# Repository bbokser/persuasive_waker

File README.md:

# persuasive_waker

Persuasive Waker is an open source hardware alarm clock that can't be snoozed or turned off. The alarm is deactivated via a remote key fob, which should be placed as far from the user's bed as possible. E.g. in the bathroom.

The KiCad design files are located in the [`hw`](hw) folder.

The STEP assembly is located [here](hw/step/).

If you just want STLs for printing, they're [here](hw/stl).

## BoM
| Item          | QTY| Source |
| --------------| ---|--|
| Case          | 1  | 3D Print |
| Screen Holder | 1  | 3D Print |
| Spacer        | 2  | 3D Print |
| M2.5x0.45-12-SHCS-SS304 | 4  | |
| M2.5x0.45-6-SHCS-SS304 | 4  | |
| M2.5x0.45-4-FHS-SS304 | 2 | |
| PRESSNUT-M2.5x0.45-SS304 | 2 | [Mouser](https://mou.sr/3FToM2v)|
| Battery Holder | 1 | [Mouser](https://mou.sr/4lddciV) |
| THRIN-M2.5X0.45-HS-PL-4L3.5D-BR | 8 | [Amazon](https://www.amazon.com/dp/B0DGPL6RWT)|
| E-Paper Display | 1 | [AliExpress](https://www.aliexpress.us/item/2251832627460771.html)|
| Key Fob | 1 | [AliExpress](https://www.aliexpress.us/item/2251832657961546.html) |
| Alarm PCB | 1 | Custom PCBA Order |
| Front Plate | 1 | Custom PCB Order  |
| Rear Plate | 1 | Custom PCB Order  |

## Mechanical Build
1. Print the case, screen holder, and two spacers.
2. Install the heat-set inserts in the case (x8).
3. Insert the PCB from the front.
4. Plug the E-paper display into the FPC connector.
5. Put the screen holder and spacers into position and then fold the display down onto it. Make sure the display is properly nestled in.
6. Holding the display down, put the front cover on.
7. Screw the front cover on with the M2.5x12 screws.
8. Using an arbor press, press the press-fit nuts into the rear cover.
9. Screw the battery holder onto the rear cover using the flat head screws and loctite. Insert AA batteries.
10. Plug the battery holder into the power connector on the back of the PCB.
11. Screw the rear cover on using the M2.5x6 screws.

## Firmware Setup
1. Install CircuitPython on your Pico by following [this](https://learn.adafruit.com/getting-started-with-raspberry-pi-pico-circuitpython/circuitpython) guide.
The last version tested with this device is [9.2.6.](https://adafruit-circuit-python.s3.amazonaws.com/bin/raspberry_pi_pico/en_US/adafruit-circuitpython-raspberry_pi_pico-en_US-9.2.6.uf2)

2. Install [circup](https://learn.adafruit.com/keep-your-circuitpython-libraries-on-devices-up-to-date-with-circup/prepare) on your computer.

3. Run the following commands to install all necessary libraries.

    ```
    circup bundle-add adafruit/circuitpython-fonts
    circup install adafruit_sht4x adafruit_ssd1680 adafruit_display_text adafruit_ds3231 adafruit_datetime adafruit_display_shapes font_ostrich_sans_black_24 font_ostrich_sans_black_60
    ```
4. Delete `code.py` from the Pico's storage.

5. Clone this repo onto your computer and copy+paste everything in the `src` folder to the Pico's storage.

6. The alarm clock should be functioning now.

## User Manual
See [here](user_manual.md).

### Upgrading from v3.0 to v3.1
1. Replace the old `src` files with the new ones on the `v3.1` branch.
2. Install [circup](https://learn.adafruit.com/keep-your-circuitpython-libraries-on-devices-up-to-date-with-circup/prepare) and run the following.
    ```
    circup bundle-add adafruit/circuitpython-fonts
    circup uninstall font_ostrich_sans_black_30 font_ostrich_sans_black_72
    circup install font_ostrich_sans_black_24 font_ostrich_sans_black_60
    circup update
    ```
    
    Alternatively, you can download the [requirements.txt](requirements.txt) and run the following:
    
    ```
    circup install -r /path/to/requirements.txt
    ```

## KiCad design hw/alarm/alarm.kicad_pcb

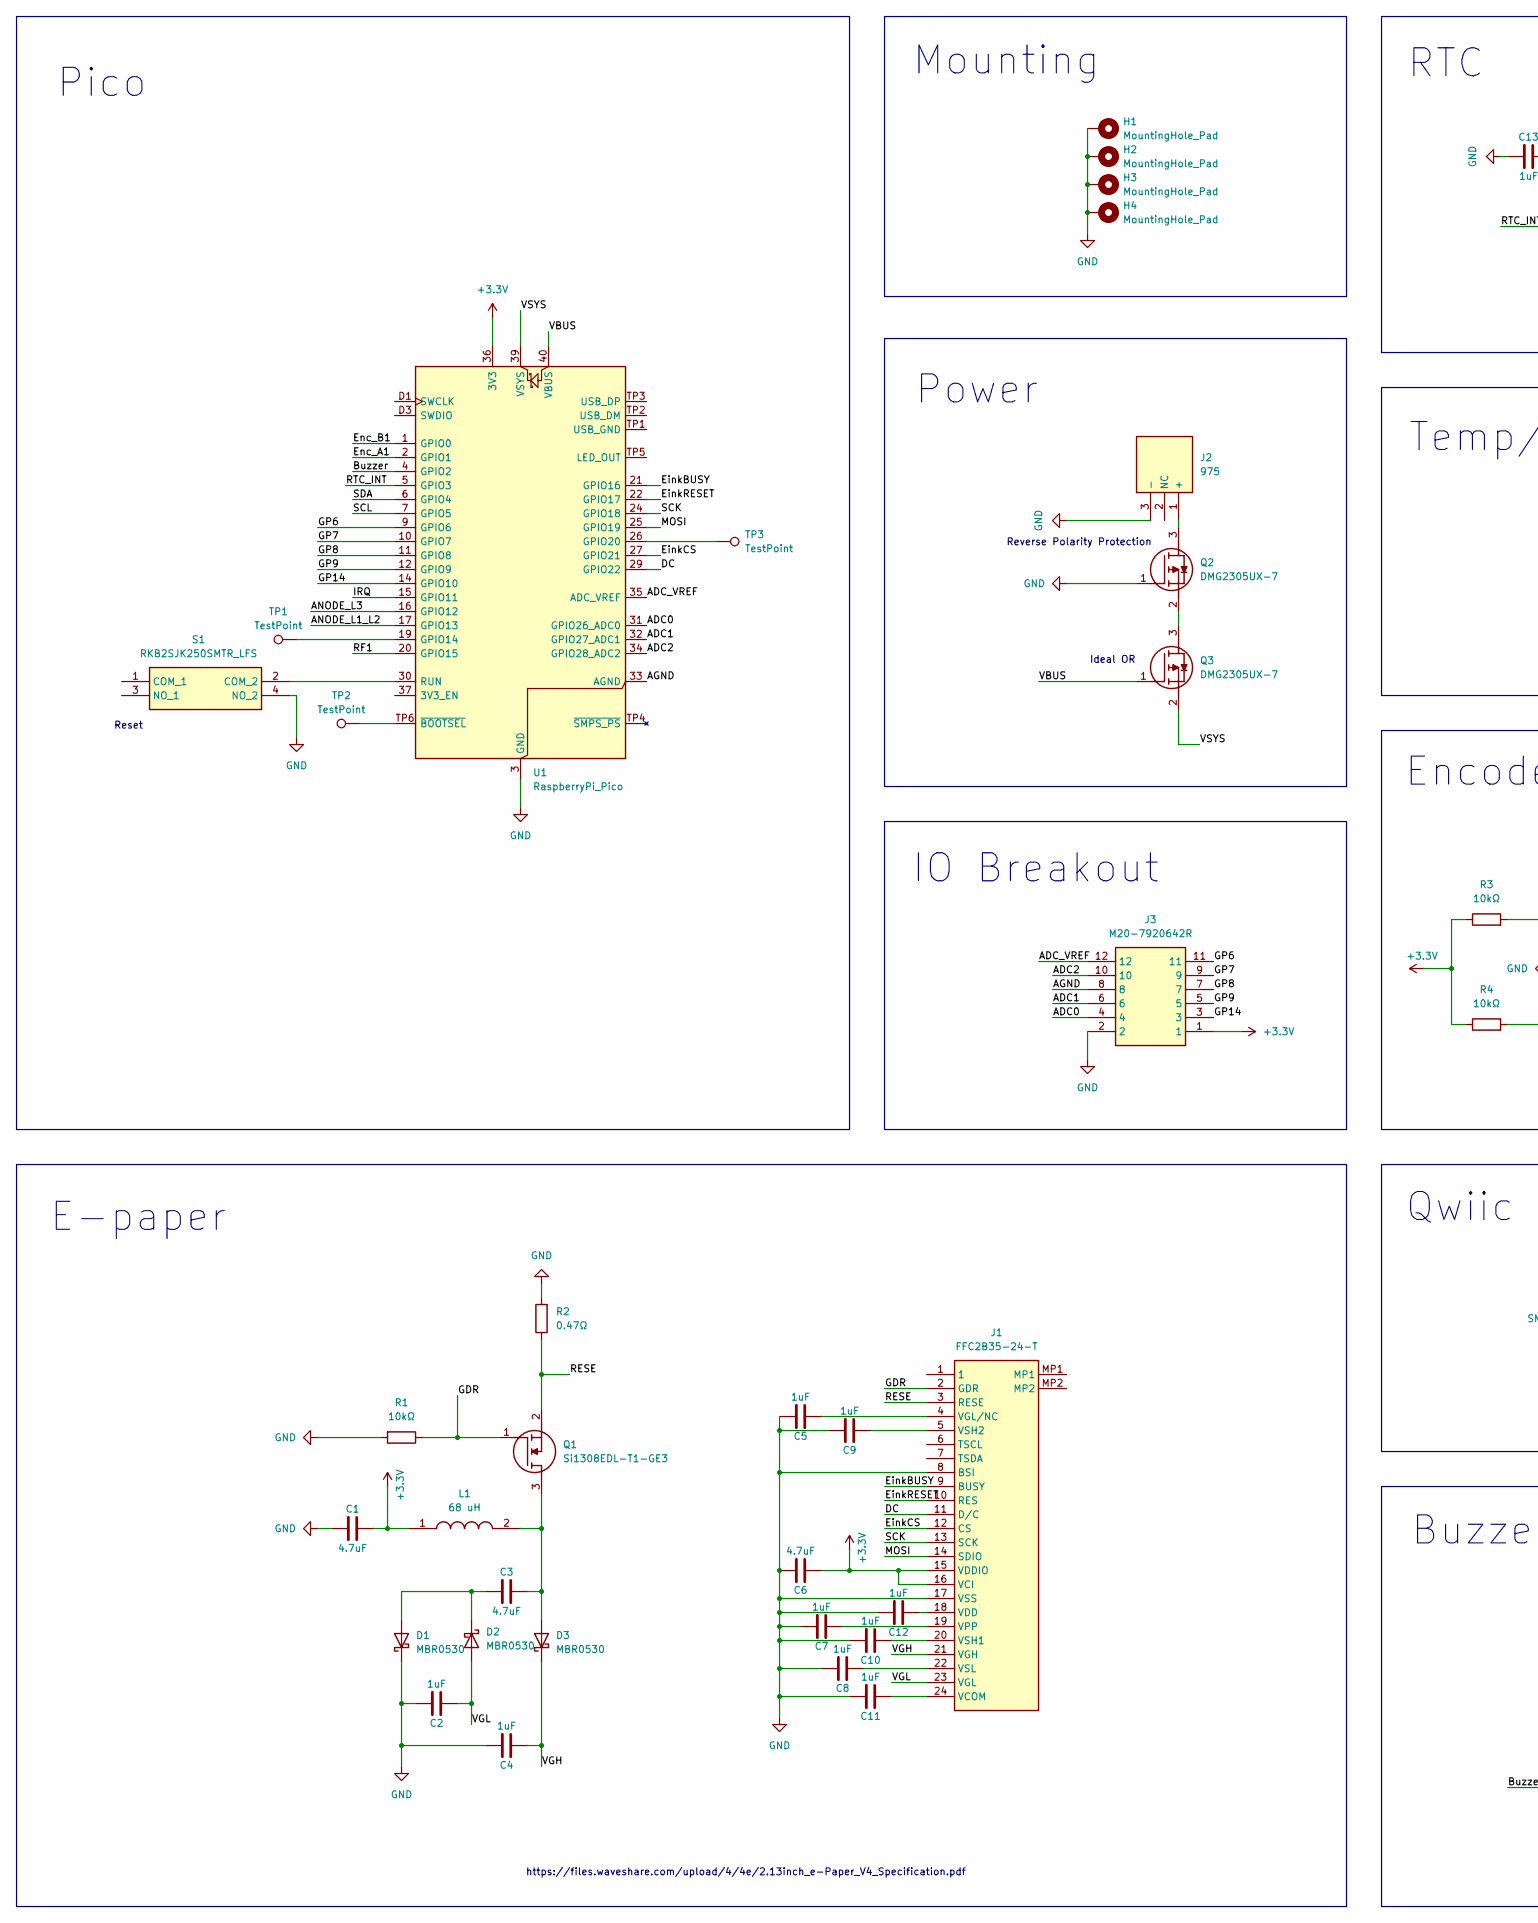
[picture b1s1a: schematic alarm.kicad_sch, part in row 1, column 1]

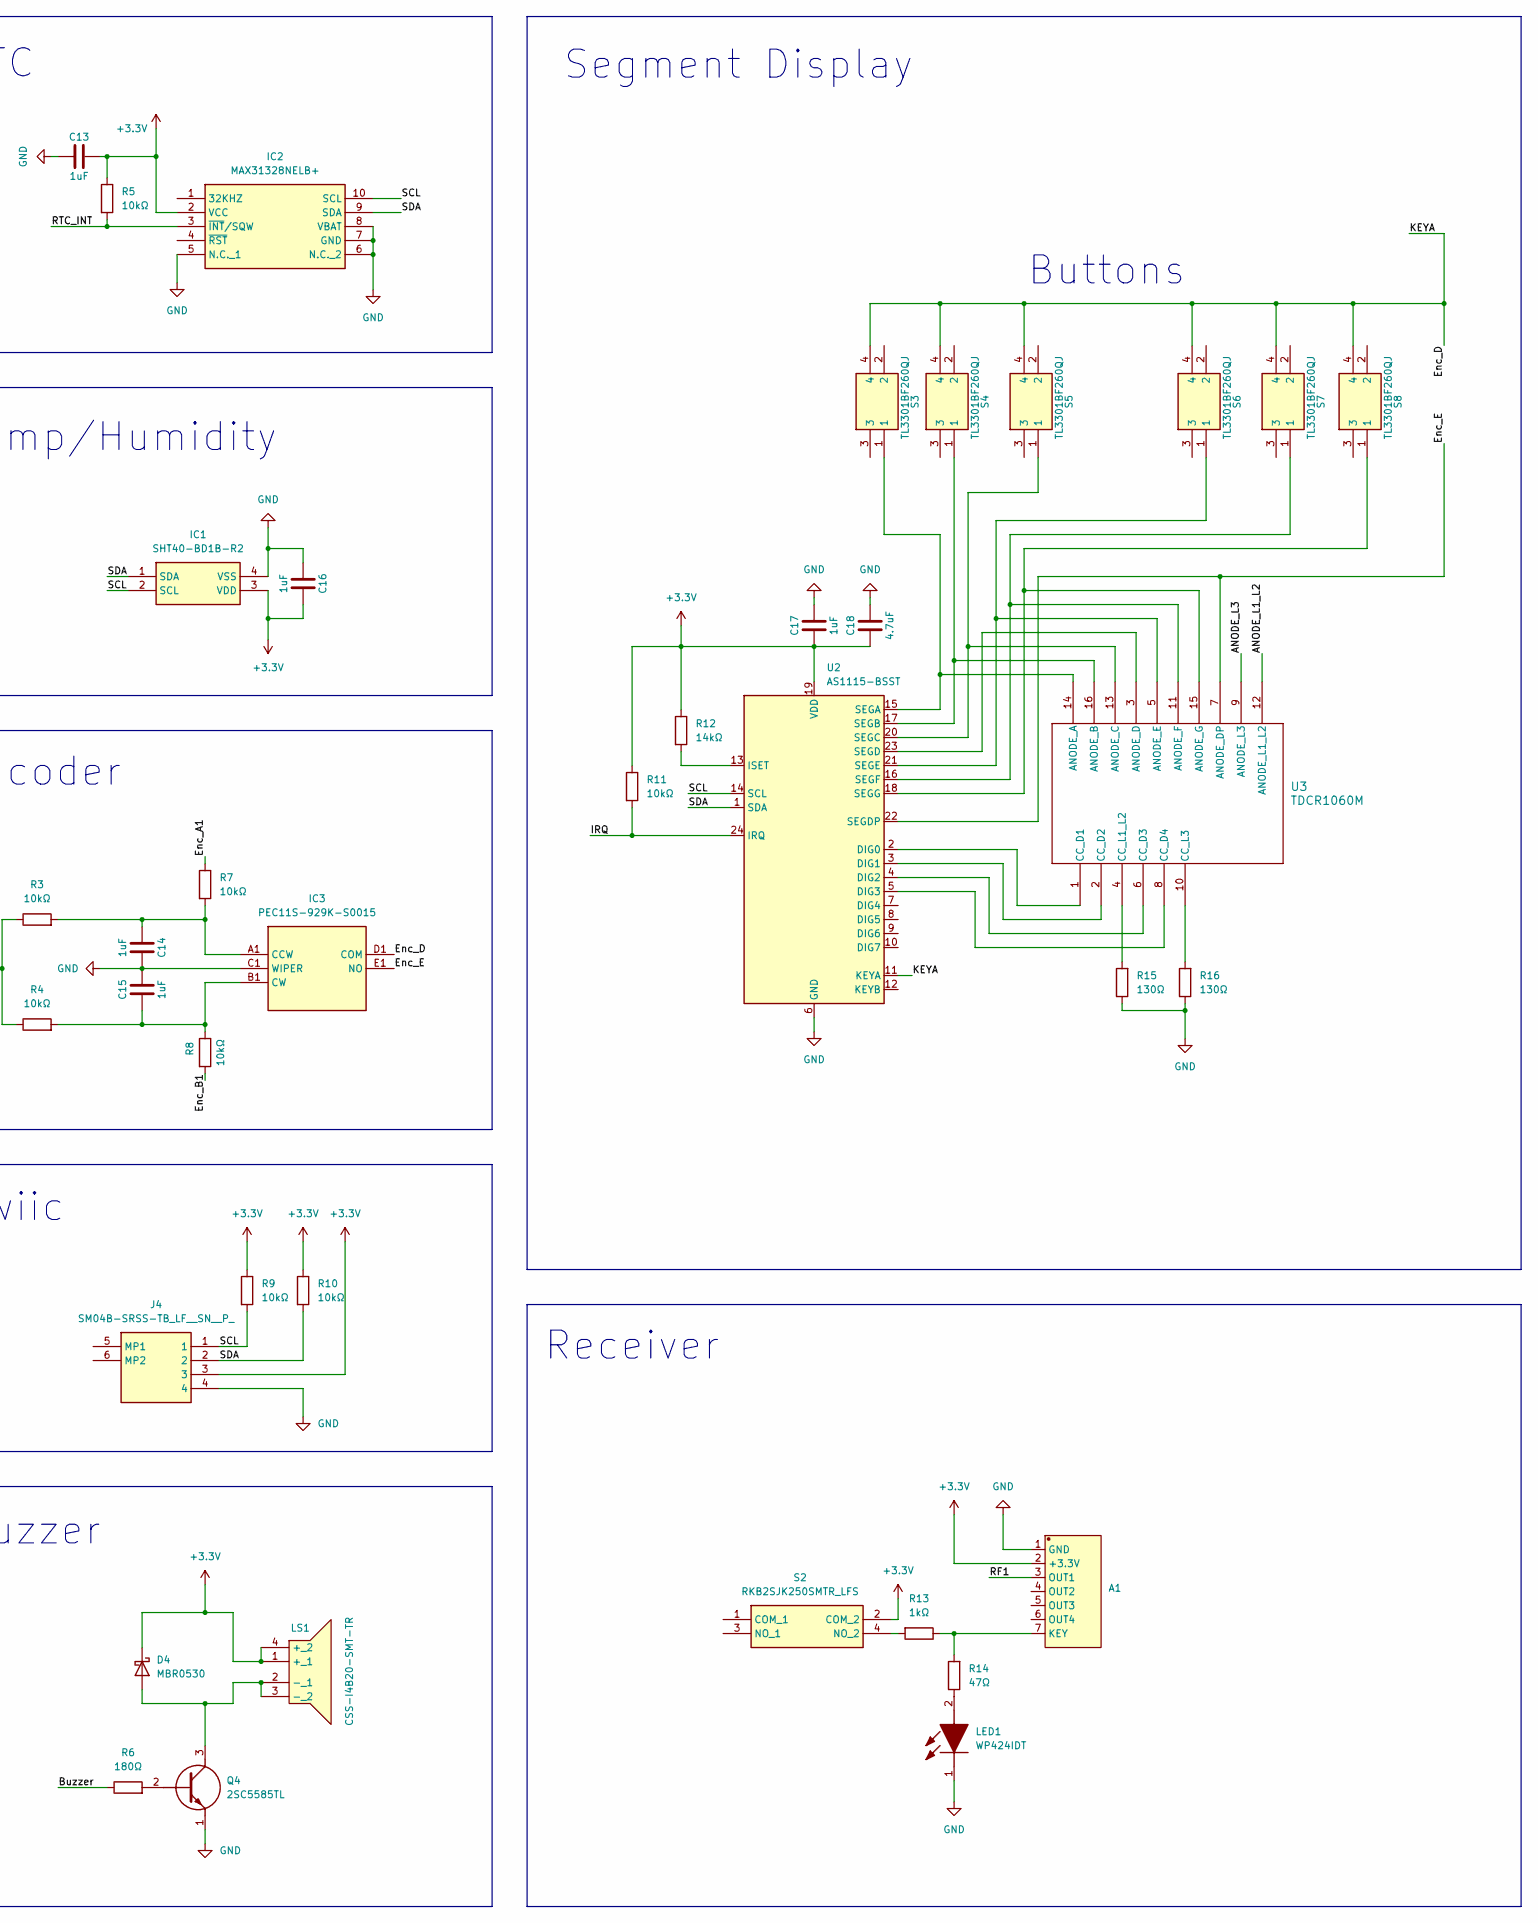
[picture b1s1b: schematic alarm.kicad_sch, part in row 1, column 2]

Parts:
A1: RX480E
C1, C3, C6, C18: 4.7uF; C_0603_1608Metric; LCSC Part # C8032
C2, C4, C5, C7, C8, C9, C10, C11, C12, C13, C14, C15, C16, C17: 1uF; C_0603_1608Metric; LCSC Part # C105524
D1, D2, D3, D4: MBR0530; D_SOD-123; LCSC Part # C77336
H1, H2, H3, H4: MountingHole_Pad; MountingHole_2.7mm_M2.5_DIN965_Pad
IC1: SHT40-BD1B-R2; SHT40BD1BR2; Mouser Part Number 403-SHT40-BD1B-R2
IC2: MAX31328NELB+; MAX31328NELB; Mouser Part Number 700-MAX31328NELB+
IC3: PEC11S-929K-S0015; PEC11S929KS0015; Mouser Part Number 652-PEC11S929K-S0015
J1: FFC2B35-24-T; FFC2B3524T; Mouser Part Number 640-FFC2B35-24-T
J2: 975; Mouser Part Number 534-975
J3: M20-7920642R; M207920642R; Manufacturer_Part_Number M20-7920642R; LCSC Part # C19188561
J4: SM04B-SRSS-TB_LF__SN__P_; SM04BSRSSTBLFSNP; Mouser Part Number 306-SM04BSRSSTBLFSNP
L1: 68 uH; INDM3225X240N; Mouser Part Number 652-CM322522-680KL
LED1: WP424IDT; Mouser Part Number 604-WP424IDT
LS1: CSS-I4B20-SMT-TR; CSSI4B20SMTTR; Mouser Part Number 490-CSS-I4B20-SMT-TR
Q1: Si1308EDL-T1-GE3; SOT65P210X110-3N; Mouser Part Number 78-SI1308EDL-T1-GE3
Q2, Q3: DMG2305UX-7; SOT96P240X115-3N; Mouser Part Number 621-DMG2305UX-7
Q4: 2SC5585TL; Mouser Part Number 755-2SC5585TL
R1, R3, R4, R5, R7, R8, R9, R10, R11: 10kΩ; R_0603_1608Metric_Pad0.98x0.95mm_HandSolder; LCSC Part # C15401
R2: 0.47Ω; R_0603_1608Metric_Pad0.98x0.95mm_HandSolder; LCSC Part # C23411
R6: 180Ω; R_0603_1608Metric_Pad0.98x0.95mm_HandSolder; LCSC Part # C100819
R12: 14kΩ; R_0603_1608Metric_Pad0.98x0.95mm_HandSolder; LCSC Part # C137795
R13: 1kΩ; R_0603_1608Metric_Pad0.98x0.95mm_HandSolder; LCSC Part # C103198
R14: 47Ω; R_0603_1608Metric_Pad0.98x0.95mm_HandSolder; LCSC Part # C1211
R15, R16: 130Ω; R_0603_1608Metric_Pad0.98x0.95mm_HandSolder; LCSC Part # C22796
S1, S2: RKB2SJK250SMTR_LFS; RKB2SJK250SMTRLFS; Mouser Part Number 611-RKB2SJK250SMTRLF
S3, S4, S5, S6, S7, S8: TL3301BF260QJ; Mouser Part Number 612-TL3301BF260QJ
TP1, TP2, TP3: TestPoint; TestPoint_Pad_1.5x1.5mm
U1: RaspberryPi_Pico; RaspberryPi_Pico_Original_SMD
U2: AS1115-BSST; QSOP-24_3.9x8.7mm_P0.635mm; LCSC Part # C2649434
U3: TDCR1060M; TDCG1060M_VIS; LCSC Part # C7067210

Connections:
+3.3V: A1.2 (+3.3V), C1.1, C6.2, C13.1, C16.1, C17.2, C18.2, D4.1 (K), IC1.3 (VDD), IC2.2 (VCC), J1.15 (VDDIO), J1.16 (VCI), J3.1, J4.3, L1.1, LS1.1 (+_1), LS1.4 (+_2), R3.1, R4.1, R5.1, R9.1, R10.1, R11.1, R12.1, S2.2 (COM_2), U1.36 (3V3), U2.19 (VDD)
/ADC0: J3.4, U1.31 (GPIO26_ADC0)
/ADC1: J3.6, U1.32 (GPIO27_ADC1)
/ADC2: J3.10, U1.34 (GPIO28_ADC2)
/ADC_VREF: J3.12, U1.35 (ADC_VREF)
/AGND: J3.8, U1.33 (AGND)
/ANODE_L1_L2: U1.17 (GPIO13), U3.12 (ANODE_L1_L2)
/ANODE_L3: U1.16 (GPIO12), U3.9 (ANODE_L3)
/Buzzer: R6.1, U1.4 (GPIO2)
/DC: J1.11 (D/C), U1.29 (GPIO22)
/EinkBUSY: J1.9 (BUSY), U1.21 (GPIO16)
/EinkCS: J1.12 (CS), U1.27 (GPIO21)
/EinkRESET: J1.10 (RES), U1.22 (GPIO17)
/Enc_A1: R7.1, U1.2 (GPIO1)
/Enc_B1: R8.2, U1.1 (GPIO0)
/Enc_D: IC3.D1 (COM), S3.4, S4.4, S5.4, S6.4, S7.4, S8.4, U2.11 (KEYA)
/Enc_E: IC3.E1 (NO), U2.22 (SEGDP), U3.7 (ANODE_DP)
/GDR: J1.2 (GDR), Q1.1 (G), R1.1
/GP6: J3.11, U1.9 (GPIO6)
/GP7: J3.9, U1.10 (GPIO7)
/GP8: J3.7, U1.11 (GPIO8)
/GP9: J3.5, U1.12 (GPIO9)
/GP14: J3.3, U1.14 (GPIO10)
/IRQ: R11.2, U1.15 (GPIO11), U2.24 (IRQ)
/MOSI: J1.14 (SDIO), U1.25 (GPIO19)
/RESE: J1.3 (RESE), Q1.2 (S), R2.1
/RF1: A1.3 (OUT1), U1.20 (GPIO15)
/RTC_INT: IC2.3 (~INT/SQW), R5.2, U1.5 (GPIO3)
/SCK: J1.13 (SCK), U1.24 (GPIO18)
/SCL: IC1.2 (SCL), IC2.10 (SCL), J4.1, R9.2, U1.7 (GPIO5), U2.14 (SCL)
/SDA: IC1.1 (SDA), IC2.9 (SDA), J4.2, R10.2, U1.6 (GPIO4), U2.1 (SDA)
/VBUS: Q3.1 (G), U1.40 (VBUS)
/VGH: C4.2, D3.1 (K), J1.21 (VGH)
/VGL: C2.2, D2.2 (A), J1.23 (VGL)
/VSYS: Q3.2 (S), U1.39 (VSYS)
GND: A1.1 (GND), C1.2, C2.1, C4.1, C5.1, C6.1, C7.1, C8.1, C9.1, C10.1, C11.1, C12.1, C13.2, C14.1, C15.1, C16.2, C17.1, C18.1, D1.1 (K), H1.1, H2.1, H3.1, H4.1, IC1.4 (VSS), IC2.5 (N.C._1), IC2.6 (N.C._2), IC2.7 (GND), IC2.8 (VBAT), IC3.C1 (WIPER), J1.8 (BSI), J1.17 (VSS), J2.3 (-), J3.2, J4.4, LED1.1 (K), Q2.1 (G), Q4.1 (E), R1.2, R2.2, R15.1, R16.1, S1.4 (NO_2), U1.3 (GND), U1.8 (GND), U1.13 (GND), U1.18 (GND), U1.23 (GND), U1.28 (GND), U1.38 (GND), U1.D2 (GND), U2.6 (GND)
unnamed: A1.7 (KEY), R13.1, R14.2
unnamed: C3.2, D1.2 (A), D2.1 (K)
unnamed: C3.1, D3.2 (A), L1.2, Q1.3 (D)
unnamed: D4.2 (A), LS1.2 (-_1), LS1.3 (-_2), Q4.3 (C)
unnamed: C14.2, IC3.A1 (CCW), R3.2, R7.2
unnamed: C15.2, IC3.B1 (CW), R4.2, R8.1
unnamed: C11.2, J1.24 (VCOM)
unnamed: C12.2, J1.18 (VDD)
unnamed: C5.2, J1.4 (VGL/NC)
unnamed: C7.2, J1.19 (VPP)
unnamed: C10.2, J1.20 (VSH1)
unnamed: C9.2, J1.5 (VSH2)
unnamed: C8.2, J1.22 (VSL)
unnamed: J2.1 (+), Q2.3 (D)
unnamed: LED1.2 (A), R14.1
unnamed: Q2.2 (S), Q3.3 (D)
unnamed: Q4.2 (B), R6.2
unnamed: S1.2 (COM_2), U1.30 (RUN)
unnamed: R13.2, S2.4 (NO_2)
unnamed: TP1.1, U1.19 (GPIO14)
unnamed: TP3.1, U1.26 (GPIO20)
unnamed: TP2.1, U1.TP6 (~BOOTSEL)
unnamed: U2.2 (DIG0), U3.1 (CC_D1)
unnamed: U2.3 (DIG1), U3.2 (CC_D2)
unnamed: U2.4 (DIG2), U3.6 (CC_D3)
unnamed: U2.5 (DIG3), U3.8 (CC_D4)
unnamed: R12.2, U2.13 (ISET)
unnamed: S3.1, U2.15 (SEGA), U3.14 (ANODE_A)
unnamed: S4.1, U2.17 (SEGB), U3.16 (ANODE_B)
unnamed: S5.1, U2.20 (SEGC), U3.13 (ANODE_C)
unnamed: U2.23 (SEGD), U3.3 (ANODE_D)
unnamed: S6.1, U2.21 (SEGE), U3.5 (ANODE_E)
unnamed: S7.1, U2.16 (SEGF), U3.11 (ANODE_F)
unnamed: S8.1, U2.18 (SEGG), U3.15 (ANODE_G)
unnamed: R15.2, U3.4 (CC_L1_L2)
unnamed: R16.2, U3.10 (CC_L3)

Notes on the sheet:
Receiver
IO Breakout
Power
https://files.waveshare.com/upload/4/4e/2.13inch_e-Paper_V4_Specification.pdf
Mounting
Ideal OR
Buttons
RTC
Segment Display
Buzzer
Encoder
Temp/Humidity
Qwiic
E-paper
Pico
Reset
Reverse Polarity Protection

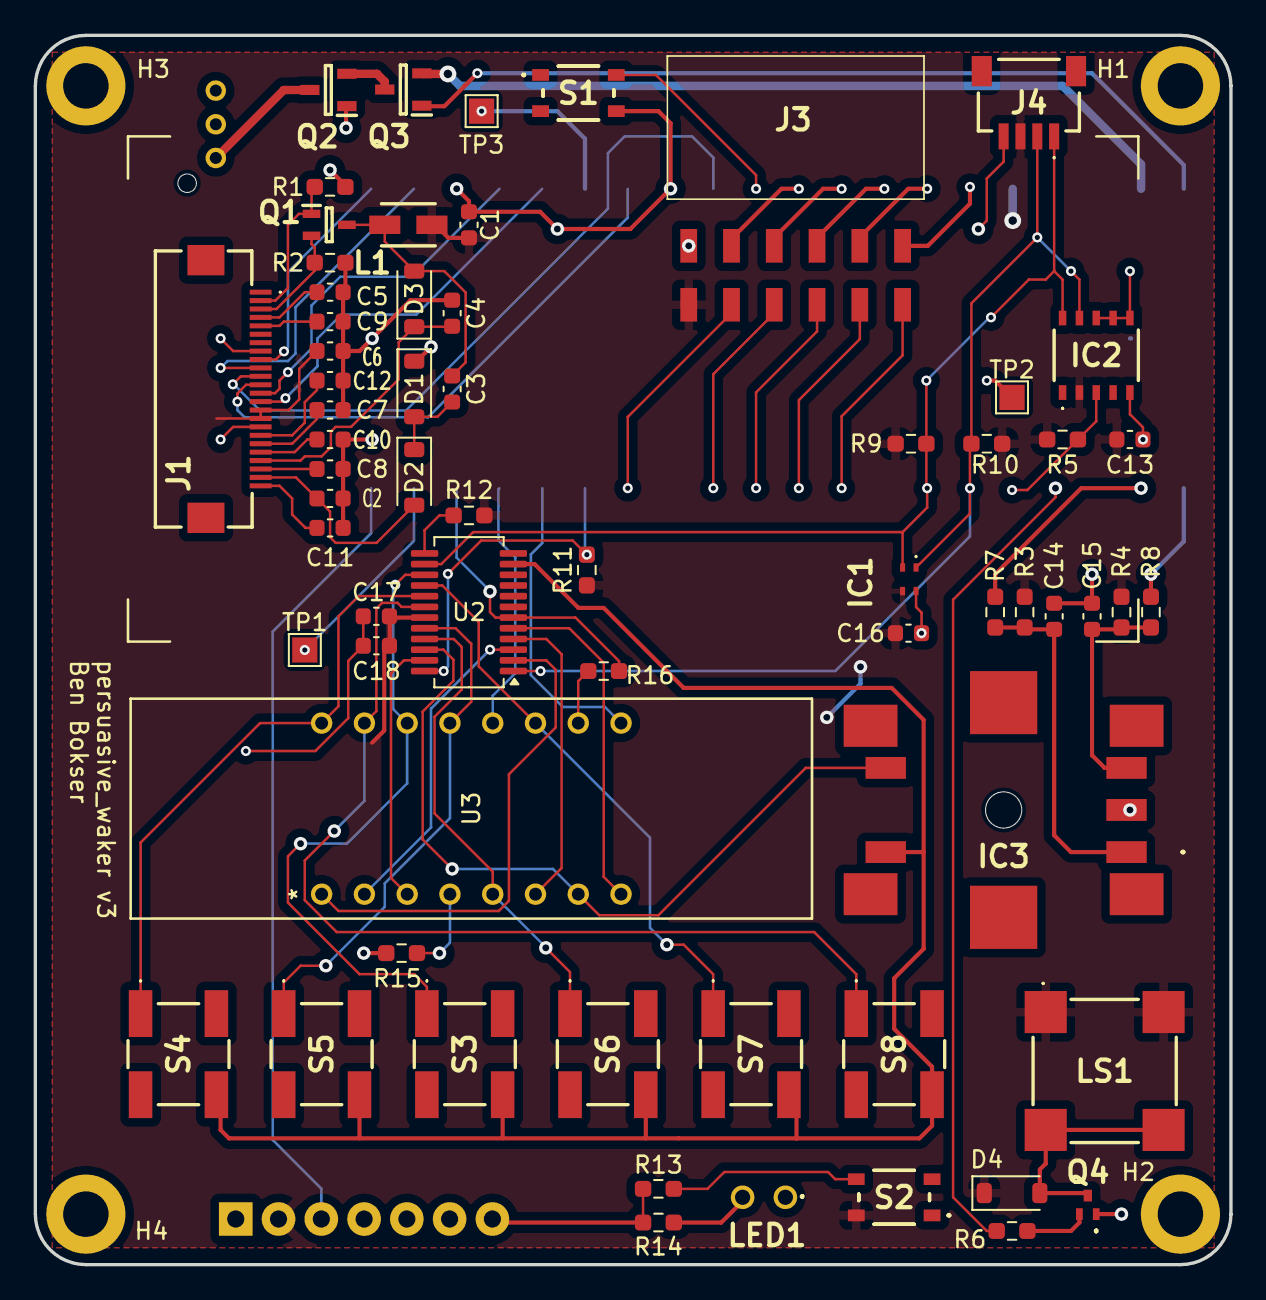
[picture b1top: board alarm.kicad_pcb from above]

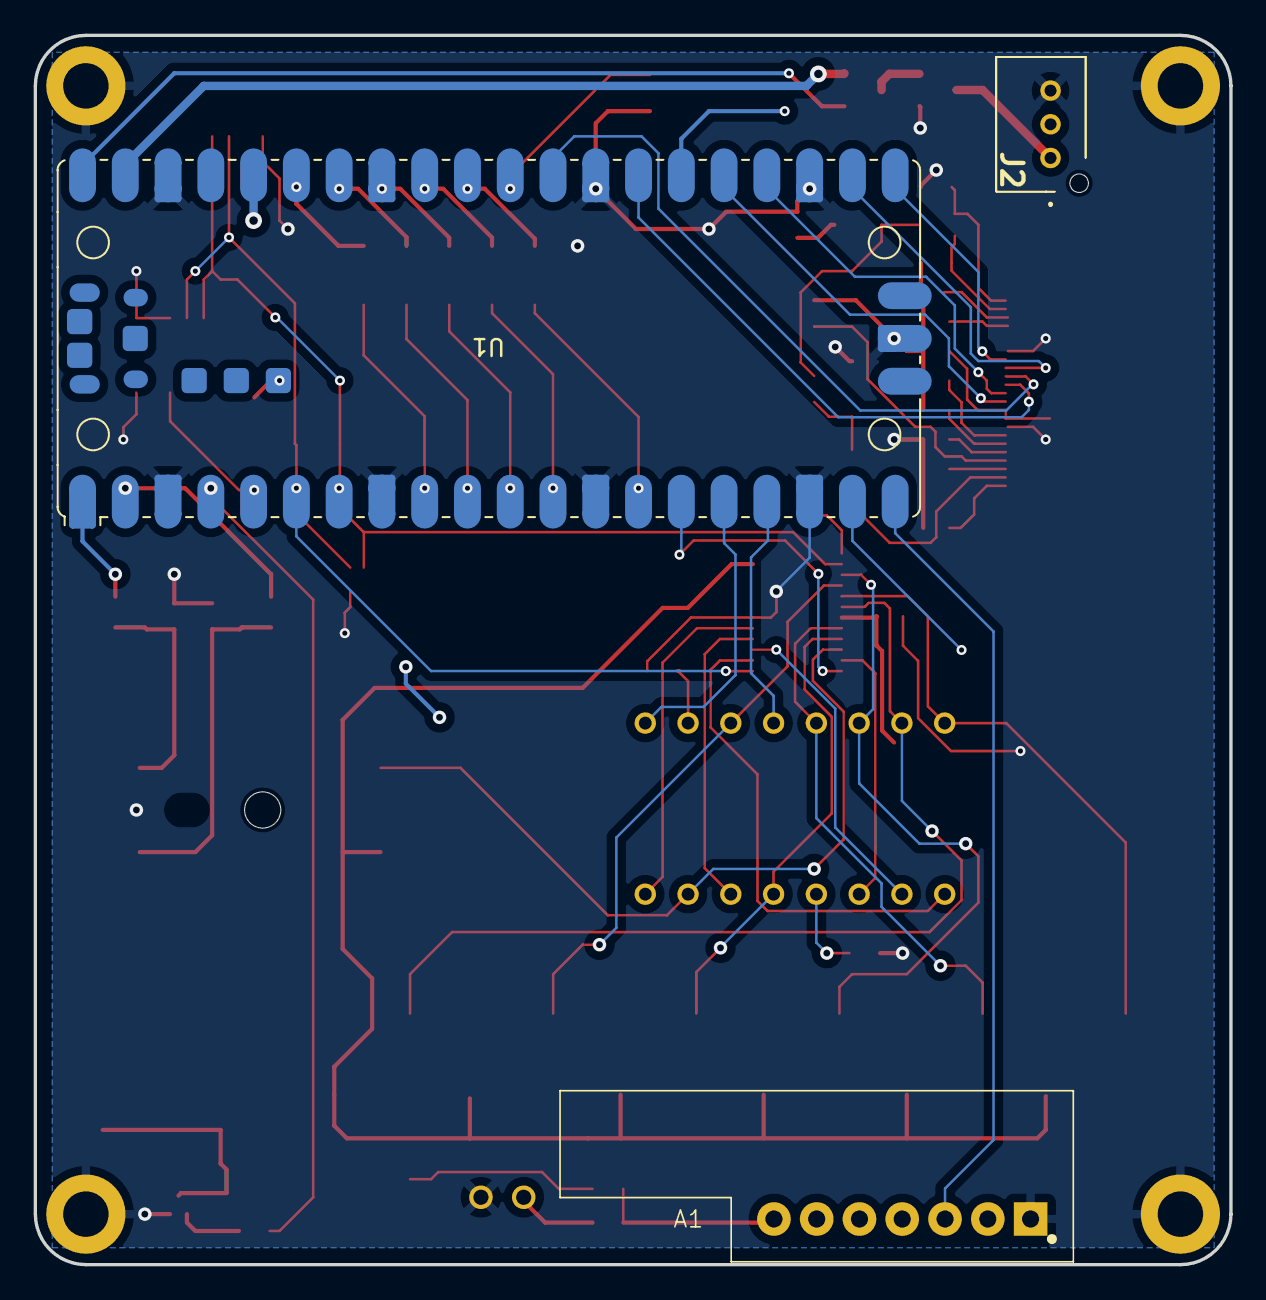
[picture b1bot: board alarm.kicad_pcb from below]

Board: 2 copper layers, 71.0 x 73.0 mm, 71 parts (3 on the bottom side), 72 nets.

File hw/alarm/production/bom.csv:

Designator,Footprint,Quantity,Value,LCSC Part #
"C1, C18, C3, C6",603,4,4.7uF,C8032
"C10, C11, C12, C13, C14, C15, C16, C17, C2, C4, C5, C7, C8, C9",603,14,1uF,C105524
"D1, D2, D3, D4",D_SOD-123,4,MBR0530,C77336
IC1,SHT40BD1BR2,1,SHT40-BD1B-R2,C7461849
IC2,MAX31328NELB,1,MAX31328NELB+,C3303818
IC3,PEC11S929KS0015,1,PEC11S-929K-S0015,C5362681
J1,FFC2B3524T,1,FFC2B35-24-T,C5641278
J3,M207920642R,1,M20-7920642R,C19188561
J4,SM04BSRSSTBLFSNP,1,SM04B-SRSS-TB_LF__SN__P_,C160404
L1,INDM3225X240N,1,68 uH,C1499398
LED1,WP424IDT,1,WP424IDT,C5878956
LS1,CSSI4B20SMTTR,1,CSS-I4B20-SMT-TR,C7116026
Q1,SOT65P210X110-3N,1,Si1308EDL-T1-GE3,C469327
"Q2, Q3",SOT96P240X115-3N,2,DMG2305UX-7,C150470
Q4,2SC5585TL,1,2SC5585TL,C337983
"R1, R10, R11, R3, R4, R5, R7, R8, R9",603,9,10kΩ,C15401
R12,603,1,14kΩ,C137795
R13,603,1,1kΩ,C103198
R14,603,1,47Ω,C1211
"R15, R16",603,2,130Ω,C22796
R2,603,1,0.47Ω,C23411
R6,603,1,180Ω,C100819
"S1, S2",RKB2SJK250SMTRLFS,2,RKB2SJK250SMTR_LFS,C2927789
"S3, S4, S5, S7, S8, S9",TL3301BF260QJ,6,TL3301BF260QJ,C2886846
U3,QSOP-24_3.9x8.7mm_P0.635mm,1,AS1115-BSST,C2649434
U4,TDCG1060M_VIS,1,TDCR1060M,C7067210

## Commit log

2024-02-25 Get date and time display working on e-ink
2024-03-31 Add hardware RTC and segment display
2024-04-02 Add state machine
2024-04-03 Continue implementing date-setting
2024-04-04 Add inputs, implement setting changes, maxday, blinking, and more
2024-04-09 Add alarm-setting
2024-04-09 add missing variables, alarm ring
2024-04-09 Minor refactor
2024-04-14 Fix various bugs
2024-04-14 Fix suffix bug
2024-05-11 Make alarm tone raise over time
2024-05-13 Add alarm read/write from storage and IR shutoff
2024-05-18 Added IR decoding to look for specific IR signal
2024-05-29 Start hardware design
2024-06-13 Change check_ir to only look at section of pulse equal in length to reference
2024-07-15 Reorganize libraries, various updates to schematic
2024-07-18 Add segment display circuit
2024-07-25 Start board layout
2024-07-26 Continue board layout
2024-07-26 Finish board layout initial ver
2024-07-26 Minor update
2024-07-27 Make DRC-rec'd changes
2024-08-11 Add pull-ups to i2c line, fix problems with DS3231 circuit
2024-08-30 Fix alarm reset bug, add refresh timer for inkdisp
2024-09-08 Small bugfixes
2024-09-24 Cobbling together AS1115 driver
2024-09-25 Finish first version of AS1115 driver
2024-10-01 Get comms with as1115 working
2024-10-02 Get AS1115 working with segment display
2024-10-03 Fix various bugs, get time, settings to work with segment display
2024-10-12 Add battery monitoring and add winking back using digit brightness
2024-10-13 Fix a multitude of bugs
2024-10-13 Fix alarm bugs
2024-10-13 Make alarming an FSM state, fix further alarm bugs
2024-10-15 Fix numerous small bugs
2024-10-16 Start making changes for v2
2024-11-04 Finish v2 schematic and begin v2 board layout
2024-11-09 Finish most of board layout
2024-11-10 Finish board layout pending last checks
2024-11-12 Further tweaks & corrections, create production files
2024-11-14 Add connectors for unused pins
2024-11-15 Add LCSC PNs, Replace through-hole breakouts with SMD header, reannotate
2024-12-14 Update firmware for new hardware design
2024-12-14 Debugging pin changes
2024-12-16 Add debouncing for keyscan
2024-12-16 Add SHT40, colon LED, and day of the week calc
2024-12-16 Refactor
2024-12-17 Various bug fixes
2024-12-23 Major refactor of fsm
2024-12-23 Fix inkdisp issues
2024-12-23 Improvements to inkdisp
2024-12-25 Fix midnight-crossing problem, make inkdisp refresh check more efficient, and other small fixes
2024-12-30 Small improvements
2024-12-30 Improvements to UI
2024-12-30 add sensor heater functionality
2025-01-26 New solution for midnight-crossing that actually works
2025-01-27 Start work on v3.0
2025-01-29 Fix new bug involving alarm_start_day
2025-01-30 Add front plate
2025-02-02 Add front and rear plate
2025-02-04 Fix bugs in days per month and weekday calc
2025-02-18 Fix S3 wiring mistake and update library paths
2025-02-26 Update README and add user manual
2025-02-27 Small bug fixes, update manual
2025-03-01 Fix bugs involving brightness setting and blinking, disable volume ramp-up
2025-03-01 Fix apost stuck bug
2025-03-14 Fix battery calc
2025-03-15 Enhance UI aesthetics
2025-03-15 Add icons to UI
2025-03-17 Add second alarm
2025-03-17 Implementing day-of-week alarm option, minor bugs
2025-03-19 Fix various bugs, add SetUnits and SetPitch
2025-03-20 Add feature to only allow alarm setting while holding down key fob
2025-03-23 Minor weekday indexing bug
2025-04-02 Improve documentation, extend safety handshake feature to time and date buttons, reduce allowable pitch
2025-04-14 Fix minor brightness bug in SetPitch
2025-04-14 Fix brightness bug in all states
2025-04-18 Fix heating bug, update README
2025-04-18 Update README to include front and rear plates in BoM
2025-05-04 Make display update automatically on settings changes
2025-05-04 Extend automatic screen update to USB power value
2025-05-04 Fix alarm not updating to None on display when disabled
2025-07-28 Get grow light nominally working
2025-07-30 Write function for light level
2025-07-30 Small bugfix
2025-07-31 Working on 12hr option
2025-08-03 Attempt to write new alarm wday setting interface
2025-08-04 Get detailed wday selection working
2025-08-04 UI improvements
2025-08-04 Revert "Working on 12hr option"
    This reverts commit 2ed213535d87bc5191b4ca15795ca357d4d1e0eb.
2025-08-08 Fix battery graphic alignment
2025-08-08 Update README and manual
2025-08-10 Fix variable referenced before assignment bug
2025-08-15 Fix is vs == bug preventing alarm from going off
2025-08-17 Fix bug where wday set appears when alarm is disabled
2025-08-17 Walk back alarm-disable-on-reset as it may be exploited
2025-08-21 Add requirements.txt and update documentation
2025-08-21 Update user manual
2025-08-31 Add water temp probe
2025-09-17 Update light functionality and get temp probe working
2025-10-04 Add brightness_max setting
2025-12-04 Add try-except to prevent i2c reads from causing crash
2025-12-04 Change start and end time
